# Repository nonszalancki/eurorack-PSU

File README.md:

# Eurorack PSU
Simple PSU for eurorack modular synth with +12v/-12v based on LM7812 & LM7912.

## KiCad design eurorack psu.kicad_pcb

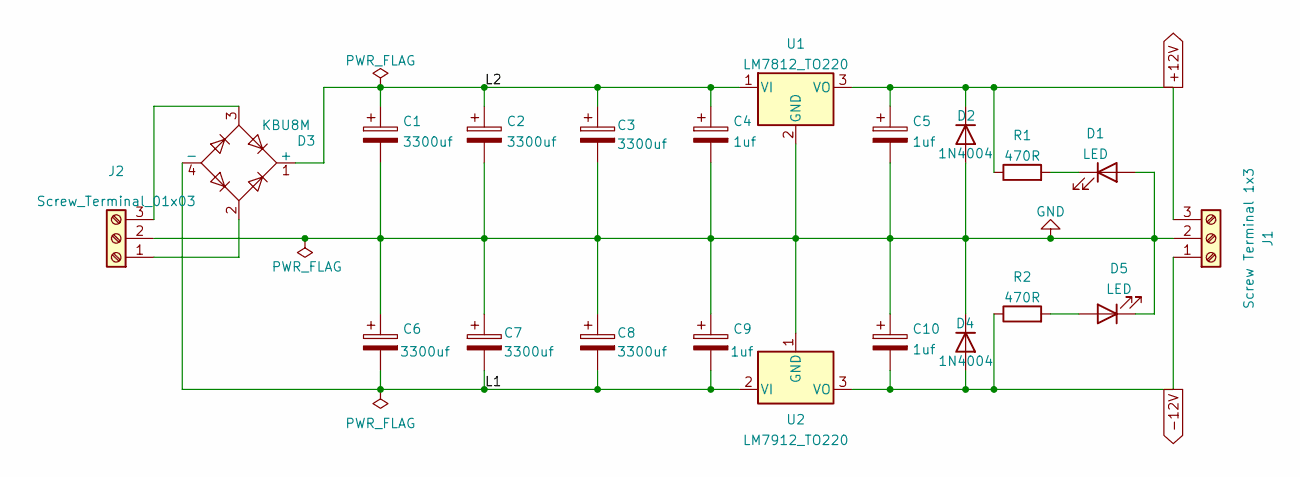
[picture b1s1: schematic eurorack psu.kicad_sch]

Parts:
C1, C2, C3, C6, C7, C8: 3300uf; CP_Radial_D18.0mm_P7.50mm
C4, C5, C9, C10: 1uf; CP_Radial_D4.0mm_P2.00mm
D1, D5: LED; LED_D3.0mm
D2, D4: 1N4004; D_DO-41_SOD81_P10.16mm_Horizontal
D3: KBU8M; Diode_Bridge_Vishay_KBU
J1: Screw Terminal 1x3; TerminalBlock_XINYA_XY301-1x3-P5.00mm
J2: Screw_Terminal_01x03; TerminalBlock_XINYA_XY301-1x3-P5.00mm
R1, R2: 470R; R_Axial_DIN0207_L6.3mm_D2.5mm_P7.62mm_Horizontal
U1: LM7812_TO220; TO-220-3_Vertical
U2: LM7912_TO220; TO-220-3_Vertical

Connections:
+12V: C5.1, D2.1 (K), J1.3, R1.1, U1.3 (VO)
-12V: C10.2, D4.2 (A), J1.1, R2.1, U2.3 (VO)
/L1: C6.2, C7.2, C8.2, C9.2, D3.4 (-), U2.2 (VI)
/L2: C1.1, C2.1, C3.1, C4.1, D3.1 (+), U1.1 (VI)
GND: C1.2, C2.2, C3.2, C4.2, C5.2, C6.1, C7.1, C8.1, C9.1, C10.1, D1.2 (A), D2.2 (A), D4.1 (K), D5.1 (K), J1.2, J2.2, U1.2 (GND), U2.1 (GND)
unnamed: D1.1 (K), R1.2
unnamed: D3.2, J2.1
unnamed: D3.3, J2.3
unnamed: D5.2 (A), R2.2

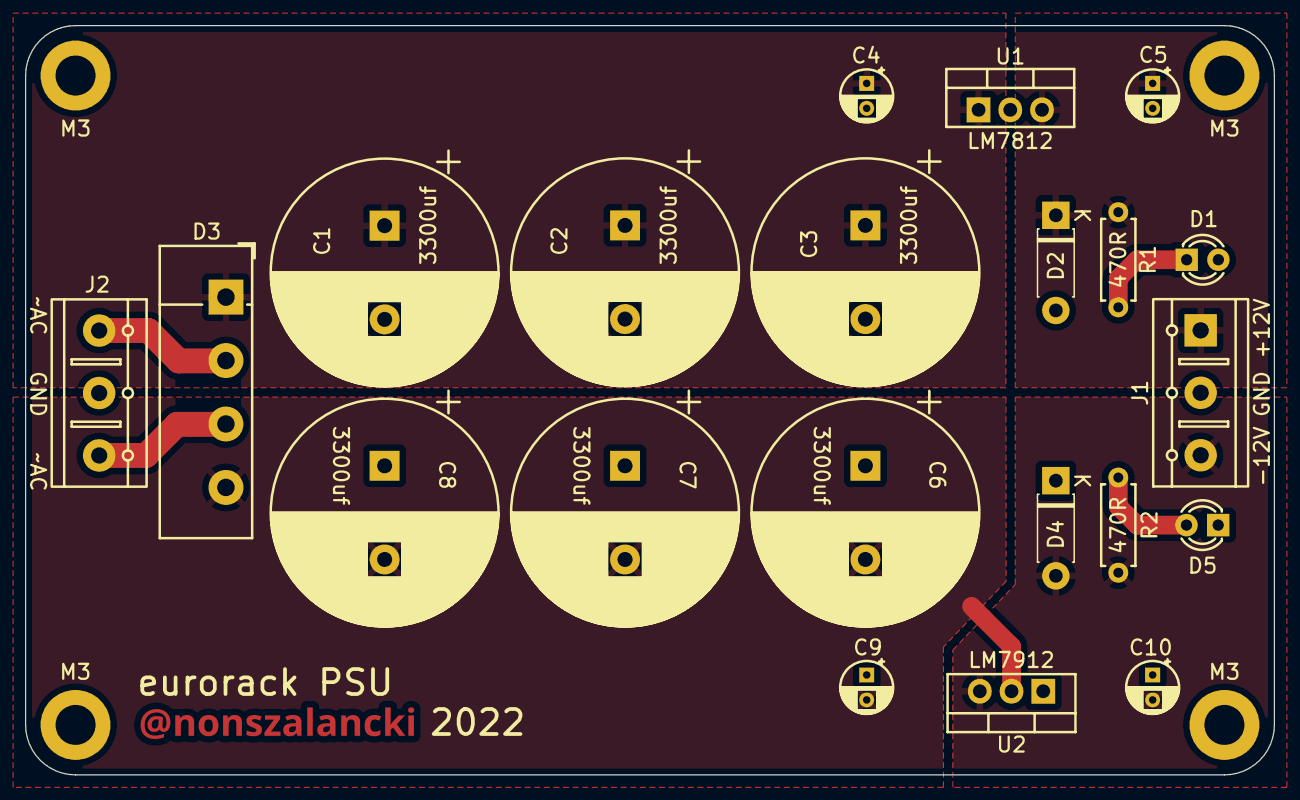
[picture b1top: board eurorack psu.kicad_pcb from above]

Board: 2 copper layers, 100.0 x 60.0 mm, 27 parts (1 on the bottom side), 9 nets.

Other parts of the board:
M3, M3#2, M3#3, M3#4: MountingHole_3.2mm_M3_DIN965_Pad
svg2mod, svg2mod#2: G***; @ nonszalancki 3-sans-serif-bold-F.Cu.svg

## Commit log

2022-04-23 added renders
2022-04-26 silkscreen changes
2022-04-26 added extension
2022-04-27 custom footprints updated
2022-05-05 minor silkscreen changes
2022-05-05 added control LEDs
2022-05-05 added PWR_FLAG to clear ERC errors
2022-05-13 updated to full bridge
2022-05-13 updated silkscreen
2022-06-10 added protection diode for 78xx & 79xx, corrected orientation of some parts
2022-07-29 Updated parts placement
2022-07-29 added screenshot of schematics
2022-08-06 PSU extension rework
2022-09-05 minor part placement changes
